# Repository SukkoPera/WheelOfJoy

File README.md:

# WheelOfJoy
WheelOfJoy is an Open Hardware 8-player joystick adapter originally designed for the Commodore 16, 116 and Plus/4.

It also works on the VIC20, Commodore 64, Commodore 128 and even on the Commodore PETs and the CBM-II and can easily be used on any platform that provides an 8-bit bidirectional port (or 5 input pins and 3 output pins).

## Summary
The original intent was to figure out how [Solder's 3-joystick Adapter](https://plus4world.powweb.com/hardware/3fach_Joystickadapter_Synergy) worked. It was pretty easy once I realized that the User Port has an output latch, but that also meant that even these 3 extra ports would suffer from the "bouncing ground" effect which prevents using powered controllers.

So I began thinking how to replicate the adapter while avoiding that and suddenly I realized that a very simple solution could be used and that it could easily be extended to support 8 joysticks while retaining compatibility with the original adapter.

One day I found out that WheelOfJoy emulation had been added to [VICE](https://vice-emu.sourceforge.io/) and that it also supported it in the C64 and other emulators, so I used that information to come up with connection diagrams for many more machines.

WheelOfJoy only supports one button per joystick, but it has [a smaller brother](https://github.com/SukkoPera/WheelOfJoyMini) with only four ports that supports 2 buttons per joystick.

The board plugs into the User Port, which means that in order to use it on a C16 or C116, you will need [a User Port card](https://github.com/SukkoPera/16up).

## Assembly
I recommend soldering all the ports first, then the resistor arrays. Speaking of those, note that while RN1-8 are *bussed*, RN9 is *independent*/*isolated*. You can replace the latter with 5 normal resistors soldered on every two adjacent holes.

The adapter can be connected to the computer through a cable with a User Port connector on one side and a male DB-15 on the other. I did this so that the adapter can be placed more freely on the table so that all players can reach it conveniently, but it also turned out to be a good choice in order to be able to use the adapter on different machines, since all you need is a different cable, while the board stays the same. So make sure to label what platform(s) your cable is made for!

The adapter-end of the cable can also be soldered directly to it, if you prefer. Pin names are noted on the board, but here's a handy table:

| DB-15 Pin # | Signal | +4 User Port Pin | PET/VIC20/C64/C128 User Port Pin | CBM-II User Port Pin | Notes                  |
|-------------|--------|------------------|----------------------------------|----------------------|------------------------|
|1	          | +5V    | 2                | 2                                | 24                   |                        |
|2	          | P0     | B                | C                                | 14                   |                        |
|3	          | P1     | K                | D                                | 13                   |                        |
|4	          | P2     | 4                | E                                | 12                   |                        |
|5	          | P3     | 5                | F                                | 11                   |                        |
|6	          | /RESET | 3                | 3                                | N/A                  | Not used by this board |
|7	          | +9V    | 10               | 10                               | N/A                  | Not used by this board |
|8	          | GND    | 1, 12, A or N    | 1, 12, A or N                    | 1 or 3               |                        |
|9	          | +5V    | 2                | 2                                | 24                   |                        |
|10	          | P4     | 6                | H                                | 10                   |                        |
|11	          | P5     | 7                | J                                | 9                    |                        |
|12	          | P6     | J                | K                                | 8                    |                        |
|13	          | P7     | F                | L                                | 7                    |                        |
|14	          | -9V    | 11               | 11                               | N/A                  | Not used by this board |
|15	          | GND    | 1, 12, A or N    | 1, 12, A or N                    | 1 or 3               |                        |

Some pins are not used because I plan to use this same pinout in the future for any other boards I may make requiring one.

**NOTE: I only tested the adapter on the C16/C116/+4. Connection information for all the other machines has been [reverse-engineered from VICE](https://sourceforge.net/p/vice-emu/code/HEAD/tree/trunk/vice/src/userport/userport_woj_joystick.c) and is provided in the hope that it will be useful, without any warranty** (Not that I provide any warranty in any case, LOL!). Please report any issues you might encounter.

[This](https://www.thingiverse.com/thing:3368773) and [these](https://www.thingiverse.com/thing:5213203) will help you make a good-looking job with your cable.

I estimate all the components required to self-build this thing to cost < 10€, probably closer to 5€ if you get them from China.

## Supported Games
Of course there isn't much software support for this at the moment but Luca/FIRE was kind enough to make [Tron 8 WOJ](https://plus4world.powweb.com/software/Tron_8_WOJ), an hack of Solder's [Tron 6](https://plus4world.powweb.com/software/Tron_6) (which can still be used in order to test the "Solder compatible mode") featuring 8 players that can all be controlled through joysticks connected to a WheelOfJoy. This is probably the first 8-player game for the x264 series ever made!

[Haegar](https://plus4world.powweb.com/members/Haegar) was the first developer to make a new game that supports WheelOfJoy natively: it is called [Bombtank](https://plus4world.powweb.com/software/Bombtank) and it supports up to 12 players!

On the Commodore 64 front, [T-Pau](https://github.com/T-Pau) has made [Joyride](https://github.com/T-Pau/Joyride/), a joystick test program that which supports many multi-player adapters, including WheelOfJoy.

Now it's up to the developers to write more party games! I'd happily send you some free PCBs if you are interested in making one, just ask!

## Programming
The board uses 5 8-to-1 multiplexers, one per direction plus one for the fire button. Channel selection happens in parallel on all multiplexers and is done with the 3 high bits of the User Port:

1. Write a value N at the User Port register depending on the port you want to read. General formula for port P ∈ [1,8] is the following:

   ```N = ((P - 1) << 5) | 0x1F```

   Or just pick your value from the following table:

   | # | Binary    | Hex| Dec | Notes                        |
   |---|-----------|----|-----|------------------------------|
   | 1 | 000 11111 | 1F |  31 |                              |
   | 2 | 001 11111 | 3F |  63 |                              |
   | 3 | 010 11111 | 5F |  95 |                              |
   | 4 | 011 11111 | 7F | 127 | Port 6 in Solder's numbering |
   | 5 | 100 11111 | 9F | 159 |                              |
   | 6 | 101 11111 | BF | 191 | Port 5 in Solder's numbering |
   | 7 | 110 11111 | DF | 223 | Port 4 in Solder's numbering |
   | 8 | 111 11111 | FF | 255 |                              |

2. Read the value of the User Port register, the lower 5 bits will report direction/button status:

   | Bit 7 | Bit 6 | Bit 5 | Bit 4 | Bit 3 | Bit 2 | Bit 1 | Bit 0 |
   |-------|-------|-------|-------|-------|-------|-------|-------|
   |   X   |   X   |   X   | Fire  | Left  | Right | Down  | Up    |

   Every bit will be 0 if the corresponding direction/button is pressed, 1 otherwise.

This means that the board works exactly like the one from Solder but the selection value is not restricted to those having exactly one zero. All values will select the corresponding port, software compatible with Solder adapter will select ports 7, 6 and 4 as 4, 5 and 6 respectively (Solder's numbering counts joystick 3 as the one available on [SID cards](https://github.com/SukkoPera/ReSeed)).

The multiplexers used on the board are analog, so the adapter is bidirectional and the ports can also be independently used as 5-bit output ports, which might open interesting possibilities...

## Compatibility
Any Atari-compliant joystick or joypad should work with this board, including Sega MegaDrive/Genesis controllers, as **pin 5 is connected to +5V**.

The latter also means that you MUST NOT use the adapter with anything that can pull pin 5 straight to ground, such as 3-button Amiga mice (what would be the purpose of that anyway?).

Also keep in mind that the User Port is only guaranteed to provide 100 mA on the +5V pin, even though I don't think there's anything actually limiting that.

## Releases
If you want to get this board produced, you are recommended to get [the latest release](https://github.com/SukkoPera/WheelOfJoy/releases) rather than the current git version, as the latter might be under development and is not guaranteed to be working.

Every release is accompanied by its Bill Of Materials (BOM) file and any relevant notes about it, which you are recommended to read carefully.

## Enclosure
A 3D-printable enclosure is currently available for this board, it was kindly contributed by Haegar and it is available on [Thingiverse](https://www.thingiverse.com/thing:6638975).

## License
The WheelOfJoy documentation, including the design itself, is copyright &copy; SukkoPera 2022 and is licensed under the [Creative Commons Attribution-NonCommercial-ShareAlike 4.0 International License](https://creativecommons.org/licenses/by-nc-sa/4.0/).

This documentation is distributed *as is* and WITHOUT ANY EXPRESS OR IMPLIED WARRANTIES whatsoever with respect to its functionality, operability or use, including, without limitation, any implied warranties OF MERCHANTABILITY, SATISFACTORY QUALITY, FITNESS FOR A PARTICULAR PURPOSE or infringement. We expressly disclaim any liability whatsoever for any direct, indirect, consequential, incidental or special damages, including, without limitation, lost revenues, lost profits, losses resulting from business interruption or loss of data, regardless of the form of action or legal theory under which the liability may be asserted, even if advised of the possibility or likelihood of such damages.

## Support the Project
If you want to get some boards manufactured, you can get them from PCBWay through this link:

You get my gratitude and cheap, professionally-made and good quality PCBs, I get some credit that will help with this and [other projects](https://www.pcbway.com/project/member/shareproject/?bmbid=41100). You won't even have to worry about the various PCB options, it's all pre-configured for you!

Also, if you still have to register, [you can use this link](https://www.pcbway.com/setinvite.aspx?inviteid=41100) to get some bonus initial credit (and yield me some more).

You can also buy me a coffee if you want:

## Credits
* Thanks to Solder for being such a prolific hacker and a great inspiration :).
* 3D model of [DB-9](https://grabcad.com/library/d-sub-9-pin-male-1) and [DB-15 connector](https://grabcad.com/library/d-sub-15-pin-female-2-lines-1) by Alex K.
* Font used for port numbers is [Agreement Signature by wepfont](https://www.fontspace.com/a-agreement-signature-font-f52534) (800 DPI).
* Font used for the logo is [Senja Santuy by Zuzulgo](https://www.fontspace.com/senja-santuy-font-f74971) (450 DPI).

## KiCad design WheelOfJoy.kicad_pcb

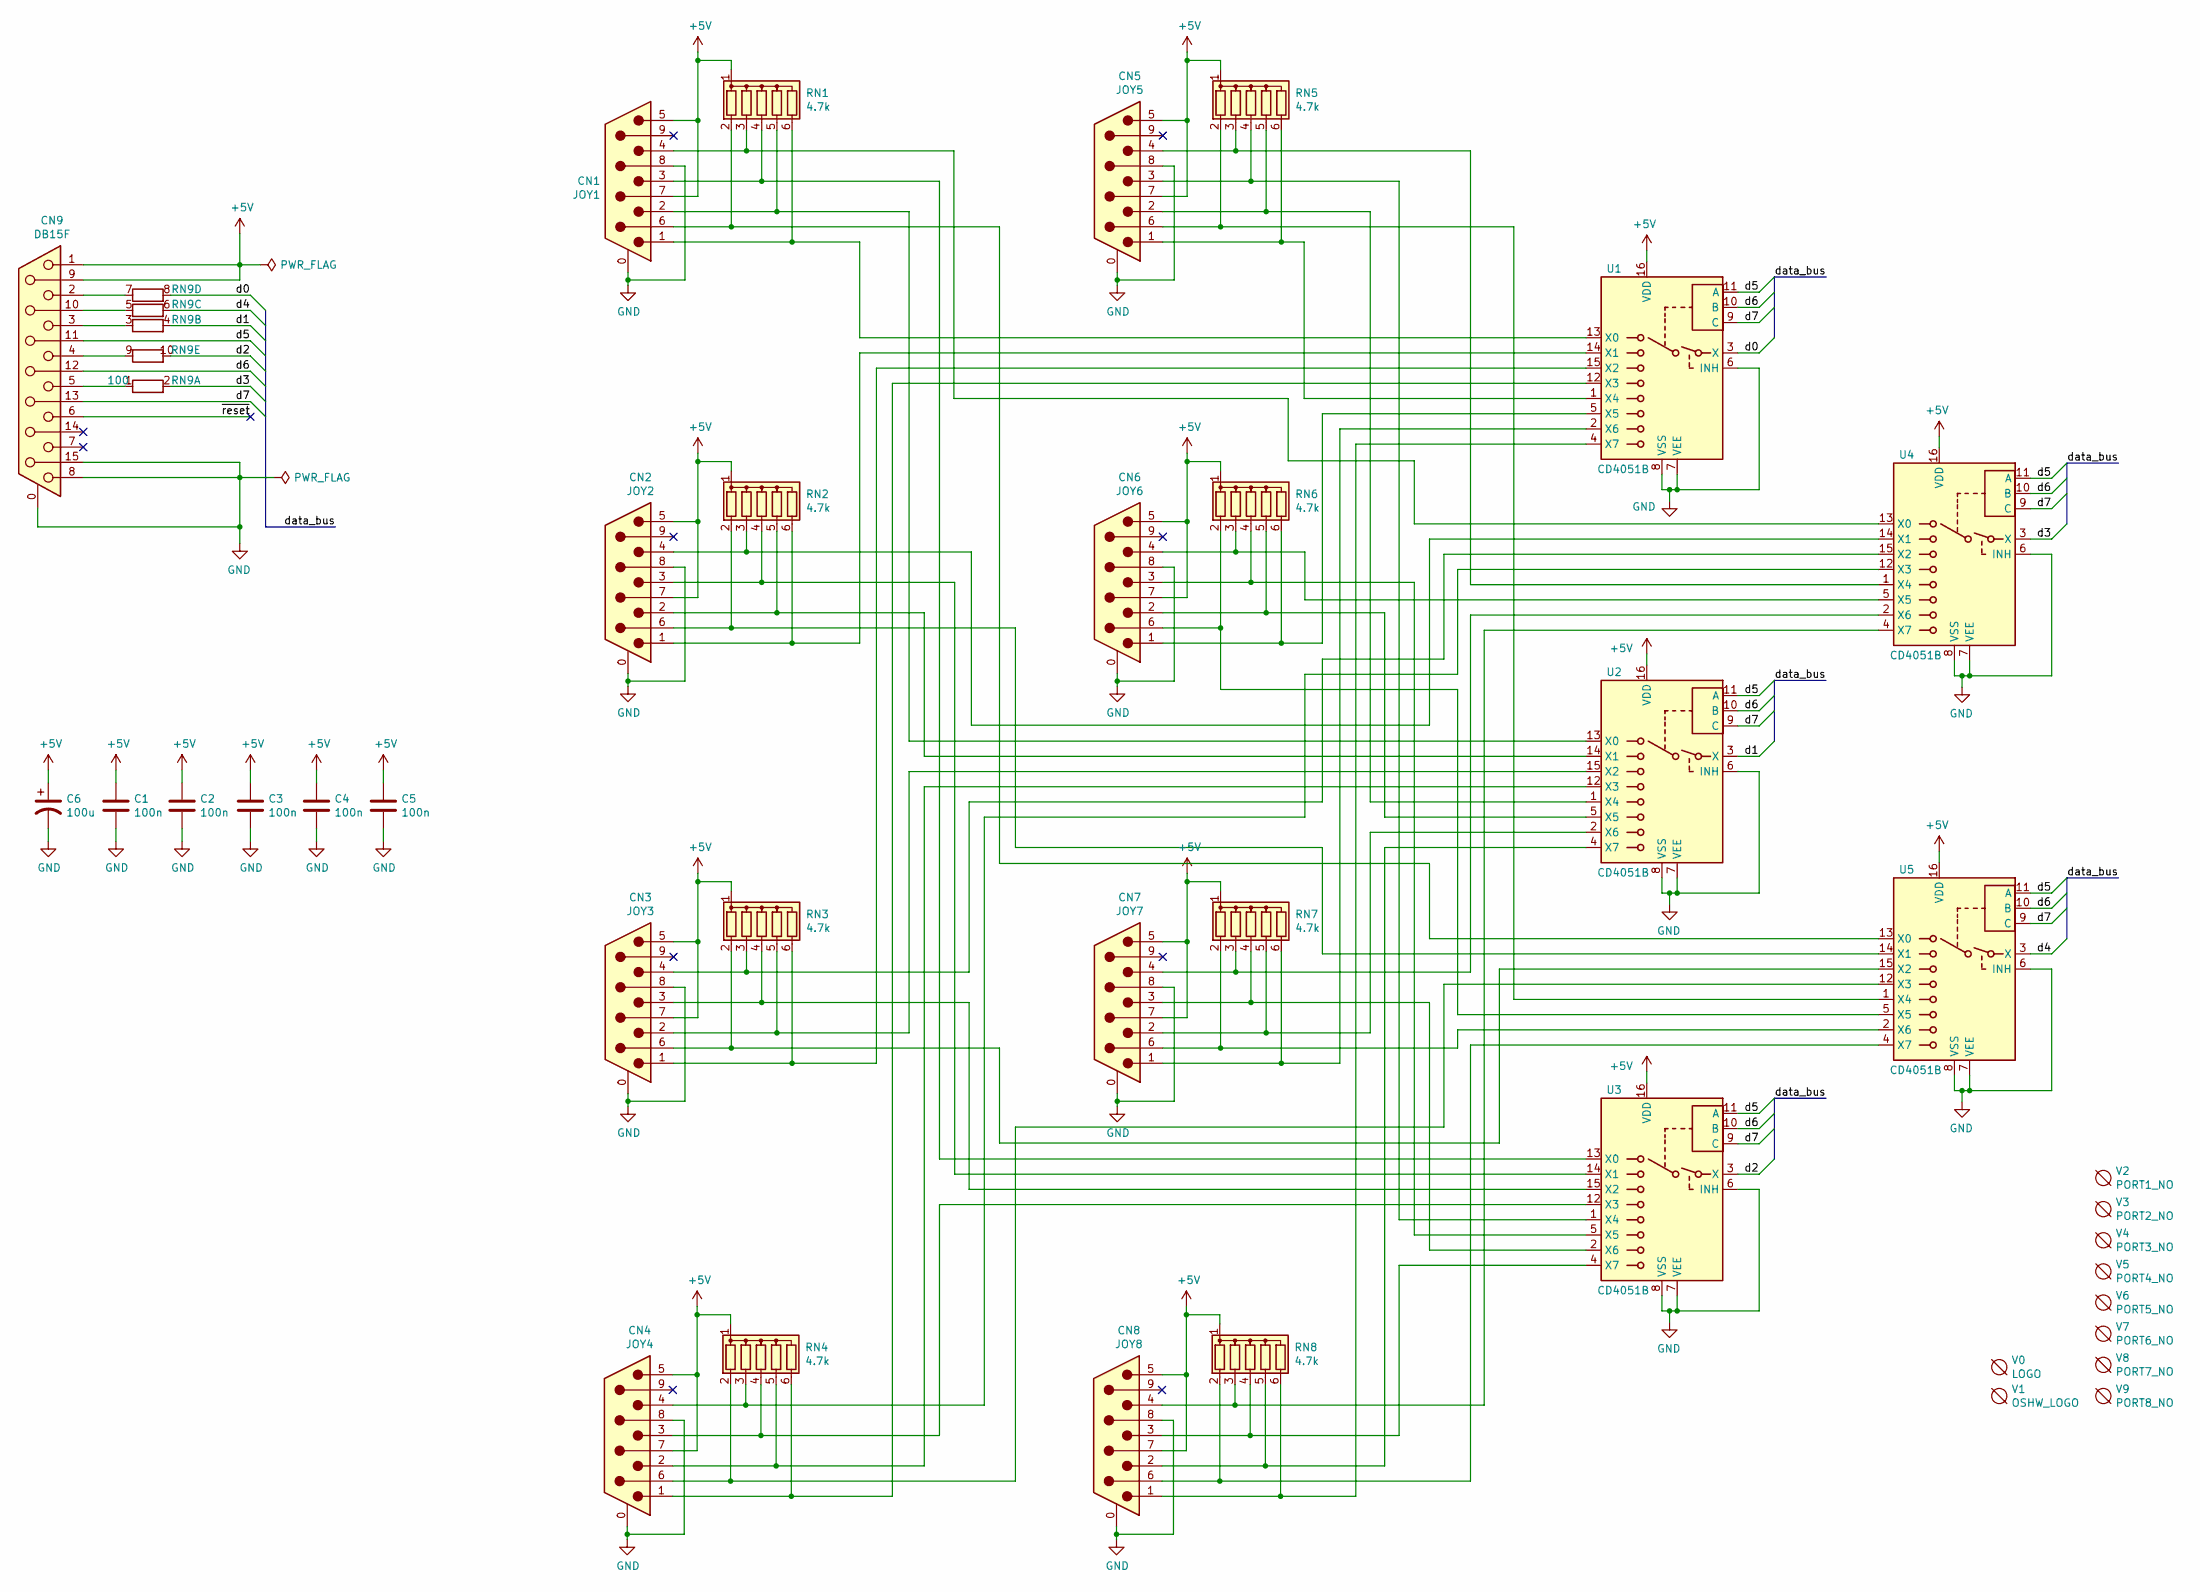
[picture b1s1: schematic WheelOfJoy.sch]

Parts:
C1, C2, C3, C4, C5: 100n; C_Disc_D7.0mm_W2.5mm_P5.00mm
C6: 100u; CP_Radial_D6.3mm_P2.50mm
CN1: JOY1; DSUB-9_Male_EdgeMount_P2.77mm
CN2: JOY2; DSUB-9_Male_EdgeMount_P2.77mm
CN3: JOY3; DSUB-9_Male_EdgeMount_P2.77mm
CN4: JOY4; DSUB-9_Male_EdgeMount_P2.77mm
CN5: JOY5; DSUB-9_Male_EdgeMount_P2.77mm
CN6: JOY6; DSUB-9_Male_EdgeMount_P2.77mm
CN7: JOY7; DSUB-9_Male_EdgeMount_P2.77mm
CN8: JOY8; DSUB-9_Male_EdgeMount_P2.77mm
CN9: DB15F; DSUB-15_Female_EdgeMount_P2.77mm
RN1, RN2, RN3, RN4, RN5, RN6, RN7, RN8: 4.7k; R_Array_SIP6
RN9: 100; R_Array_SIP10
U1, U2, U3, U4, U5: CD4051B; DIP-16_W7.62mm_Socket_LongPads
V0: LOGO; logo
V1: OSHW_LOGO; cc_by_nc_sa
V2: PORT1_NO; port1
V3: PORT2_NO; port2
V4: PORT3_NO; port3
V5: PORT4_NO; port4
V6: PORT5_NO; port5
V7: PORT6_NO; port6
V8: PORT7_NO; port7
V9: PORT8_NO; port8

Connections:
+5V: C1.1, C2.1, C3.1, C4.1, C5.1, C6.1, CN1.5, CN1.7, CN2.5, CN2.7, CN3.5, CN3.7, CN4.5, CN4.7, CN5.5, CN5.7, CN6.5, CN6.7, CN7.5, CN7.7, CN8.5, CN8.7, CN9.1, CN9.9, RN1.1 (common), RN2.1 (common), RN3.1 (common), RN4.1 (common), RN5.1 (common), RN6.1 (common), RN7.1 (common), RN8.1 (common), U1.16 (VDD), U2.16 (VDD), U3.16 (VDD), U4.16 (VDD), U5.16 (VDD)
/d0: RN9.8 (R4.2), U1.3 (X)
/d1: RN9.4 (R2.2), U2.3 (X)
/d2: RN9.10 (R5.2), U3.3 (X)
/d3: RN9.2 (R1.2), U4.3 (X)
/d4: RN9.6 (R3.2), U5.3 (X)
/d5: CN9.11 (P111), U1.11 (A), U2.11 (A), U3.11 (A), U4.11 (A), U5.11 (A)
/d6: CN9.12, U1.10 (B), U2.10 (B), U3.10 (B), U4.10 (B), U5.10 (B)
/d7: CN9.13, U1.9 (C), U2.9 (C), U3.9 (C), U4.9 (C), U5.9 (C)
GND: C1.2, C2.2, C3.2, C4.2, C5.2, C6.2, CN1.0 (PAD), CN1.8, CN2.0 (PAD), CN2.8, CN3.0 (PAD), CN3.8, CN4.0 (PAD), CN4.8, CN5.0 (PAD), CN5.8, CN6.0 (PAD), CN6.8, CN7.0 (PAD), CN7.8, CN8.0 (PAD), CN8.8, CN9.0 (PAD), CN9.8, CN9.15, U1.6 (INH), U1.7 (VEE), U1.8 (VSS), U2.6 (INH), U2.7 (VEE), U2.8 (VSS), U3.6 (INH), U3.7 (VEE), U3.8 (VSS), U4.6 (INH), U4.7 (VEE), U4.8 (VSS), U5.6 (INH), U5.7 (VEE), U5.8 (VSS)
unnamed: CN1.1, RN1.6 (R5), U1.13 (X0)
unnamed: CN1.2, RN1.5 (R4), U2.13 (X0)
unnamed: CN1.3, RN1.4 (R3), U3.13 (X0)
unnamed: CN1.4, RN1.3 (R2), U4.13 (X0)
unnamed: CN1.6, RN1.2 (R1), U5.13 (X0)
unnamed: CN2.1, RN2.6 (R5), U1.14 (X1)
unnamed: CN2.2, RN2.5 (R4), U2.14 (X1)
unnamed: CN2.3, RN2.4 (R3), U3.14 (X1)
unnamed: CN2.4, RN2.3 (R2), U4.14 (X1)
unnamed: CN2.6, RN2.2 (R1), U5.14 (X1)
unnamed: CN3.1, RN3.6 (R5), U1.15 (X2)
unnamed: CN3.2, RN3.5 (R4), U2.15 (X2)
unnamed: CN3.3, RN3.4 (R3), U3.15 (X2)
unnamed: CN3.4, RN3.3 (R2), U4.15 (X2)
unnamed: CN3.6, RN3.2 (R1), U5.15 (X2)
unnamed: CN4.1, RN4.6 (R5), U1.12 (X3)
unnamed: CN4.2, RN4.5 (R4), U2.12 (X3)
unnamed: CN4.3, RN4.4 (R3), U3.12 (X3)
unnamed: CN4.4, RN4.3 (R2), U4.12 (X3)
unnamed: CN4.6, RN4.2 (R1), U5.12 (X3)
unnamed: CN5.1, RN5.6 (R5), U1.1 (X4)
unnamed: CN5.2, RN5.5 (R4), U2.1 (X4)
unnamed: CN5.3, RN5.4 (R3), U3.1 (X4)
unnamed: CN5.4, RN5.3 (R2), U4.1 (X4)
unnamed: CN5.6, RN5.2 (R1), U5.1 (X4)
unnamed: CN6.1, RN6.6 (R5), U1.5 (X5)
unnamed: CN6.2, RN6.5 (R4), U2.5 (X5)
unnamed: CN6.3, RN6.4 (R3), U3.5 (X5)
unnamed: CN6.4, RN6.3 (R2), U4.5 (X5)
unnamed: CN6.6, RN6.2 (R1), U5.5 (X5)
unnamed: CN7.1, RN7.6 (R5), U1.2 (X6)
unnamed: CN7.2, RN7.5 (R4), U2.2 (X6)
unnamed: CN7.3, RN7.4 (R3), U3.2 (X6)
unnamed: CN7.4, RN7.3 (R2), U4.2 (X6)
unnamed: CN7.6, RN7.2 (R1), U5.2 (X6)
unnamed: CN8.1, RN8.6 (R5), U1.4 (X7)
unnamed: CN8.2, RN8.5 (R4), U2.4 (X7)
unnamed: CN8.3, RN8.4 (R3), U3.4 (X7)
unnamed: CN8.4, RN8.3 (R2), U4.4 (X7)
unnamed: CN8.6, RN8.2 (R1), U5.4 (X7)
unnamed: CN9.2, RN9.7 (R4.1)
unnamed: CN9.3, RN9.3 (R2.1)
unnamed: CN9.4, RN9.9 (R5.1)
unnamed: CN9.5, RN9.1 (R1.1)
unnamed: CN9.10, RN9.5 (R3.1)

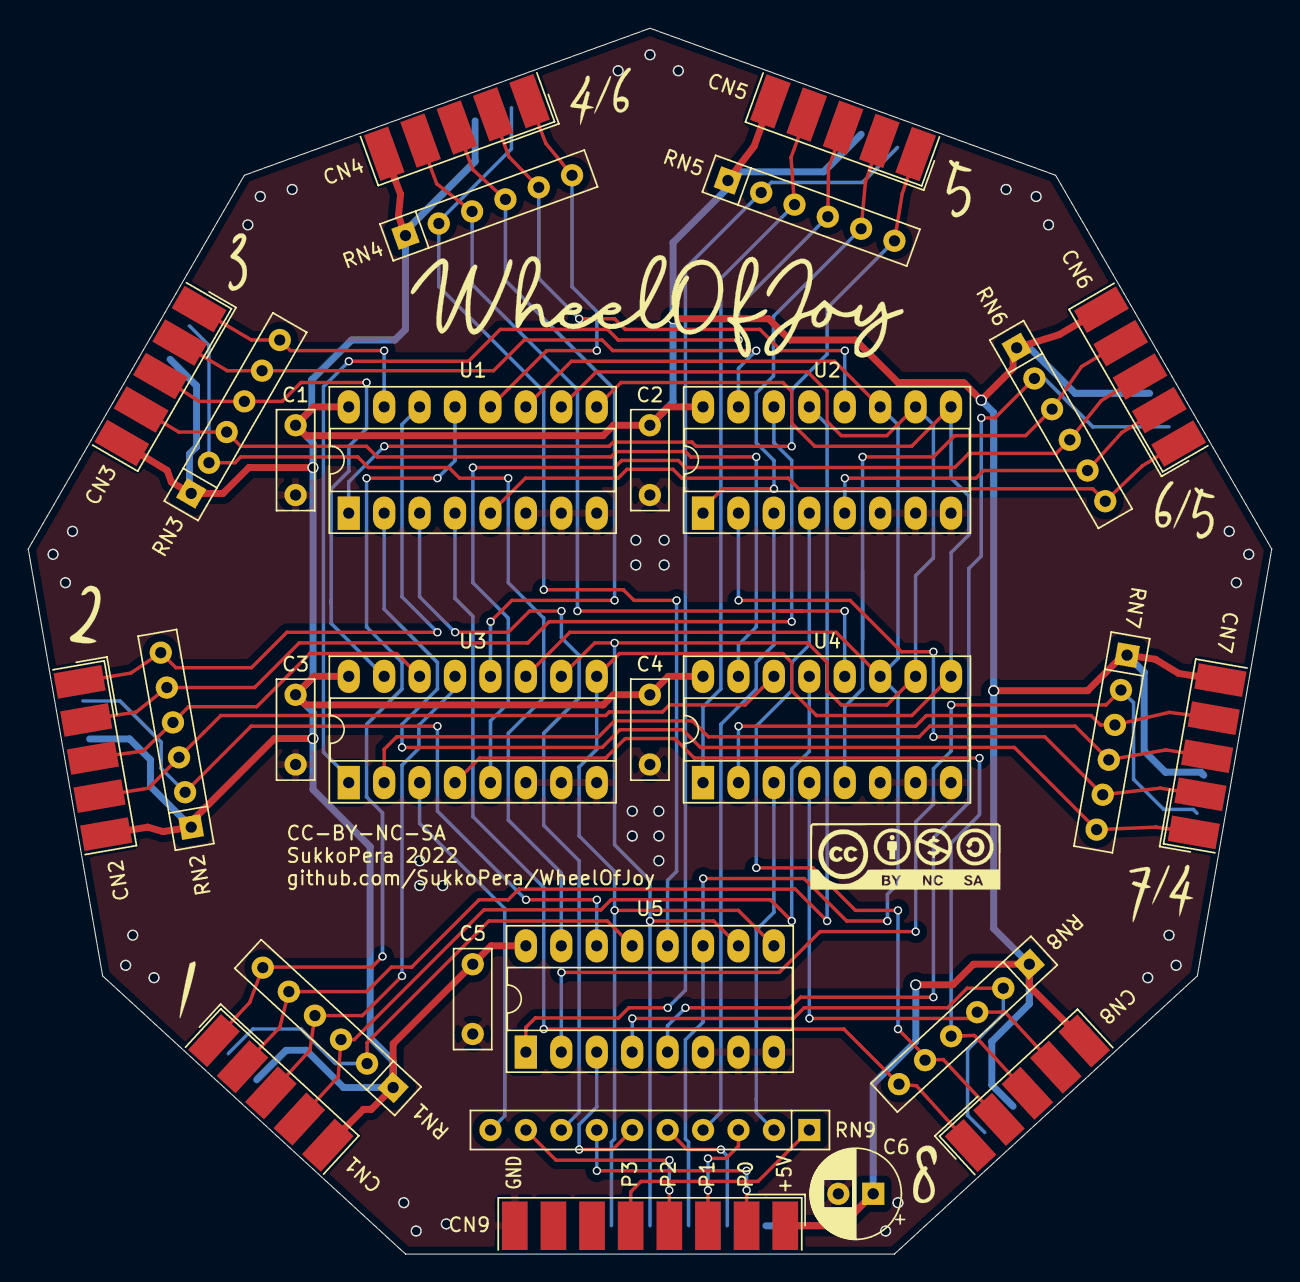
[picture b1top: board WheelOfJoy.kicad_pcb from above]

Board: 2 copper layers, 89.2 x 87.9 mm, 39 parts (0 on the bottom side), 55 nets.

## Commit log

2022-09-01 Initial layout
2022-09-01 New layout, way funnier
2022-09-02 Routing in progress
2022-09-03 Rough routing done except power
2022-09-03 Working on ground plane Top half TBD
2022-09-03 Top ground plane almost done
2022-09-04 0 unrouted! But some space for improvements left
2022-09-04 Almost there
2022-09-04 Ja ja ja
2022-09-04 Plus4Plus8 -> WheelOfJoy
2022-09-04 Embellish silkscreen
2022-09-04 Ready for V1 RC1
2022-09-13 Add series resistor on D1-D5
2022-10-23 Fix port labels And learn to count from 0 next time...
2022-11-06 Add docs
2022-11-06 Add notes on resistor arrays
2022-11-06 Fix typo
2022-11-08 Fix copyright year
2023-01-17 Add sponsor link
2024-06-01 Add links to enclosure and Bombtank
2024-06-05 Add more platforms to README.md
2026-02-13 Change coffee donation image link in README
    Updated the coffee donation link image in the README.
